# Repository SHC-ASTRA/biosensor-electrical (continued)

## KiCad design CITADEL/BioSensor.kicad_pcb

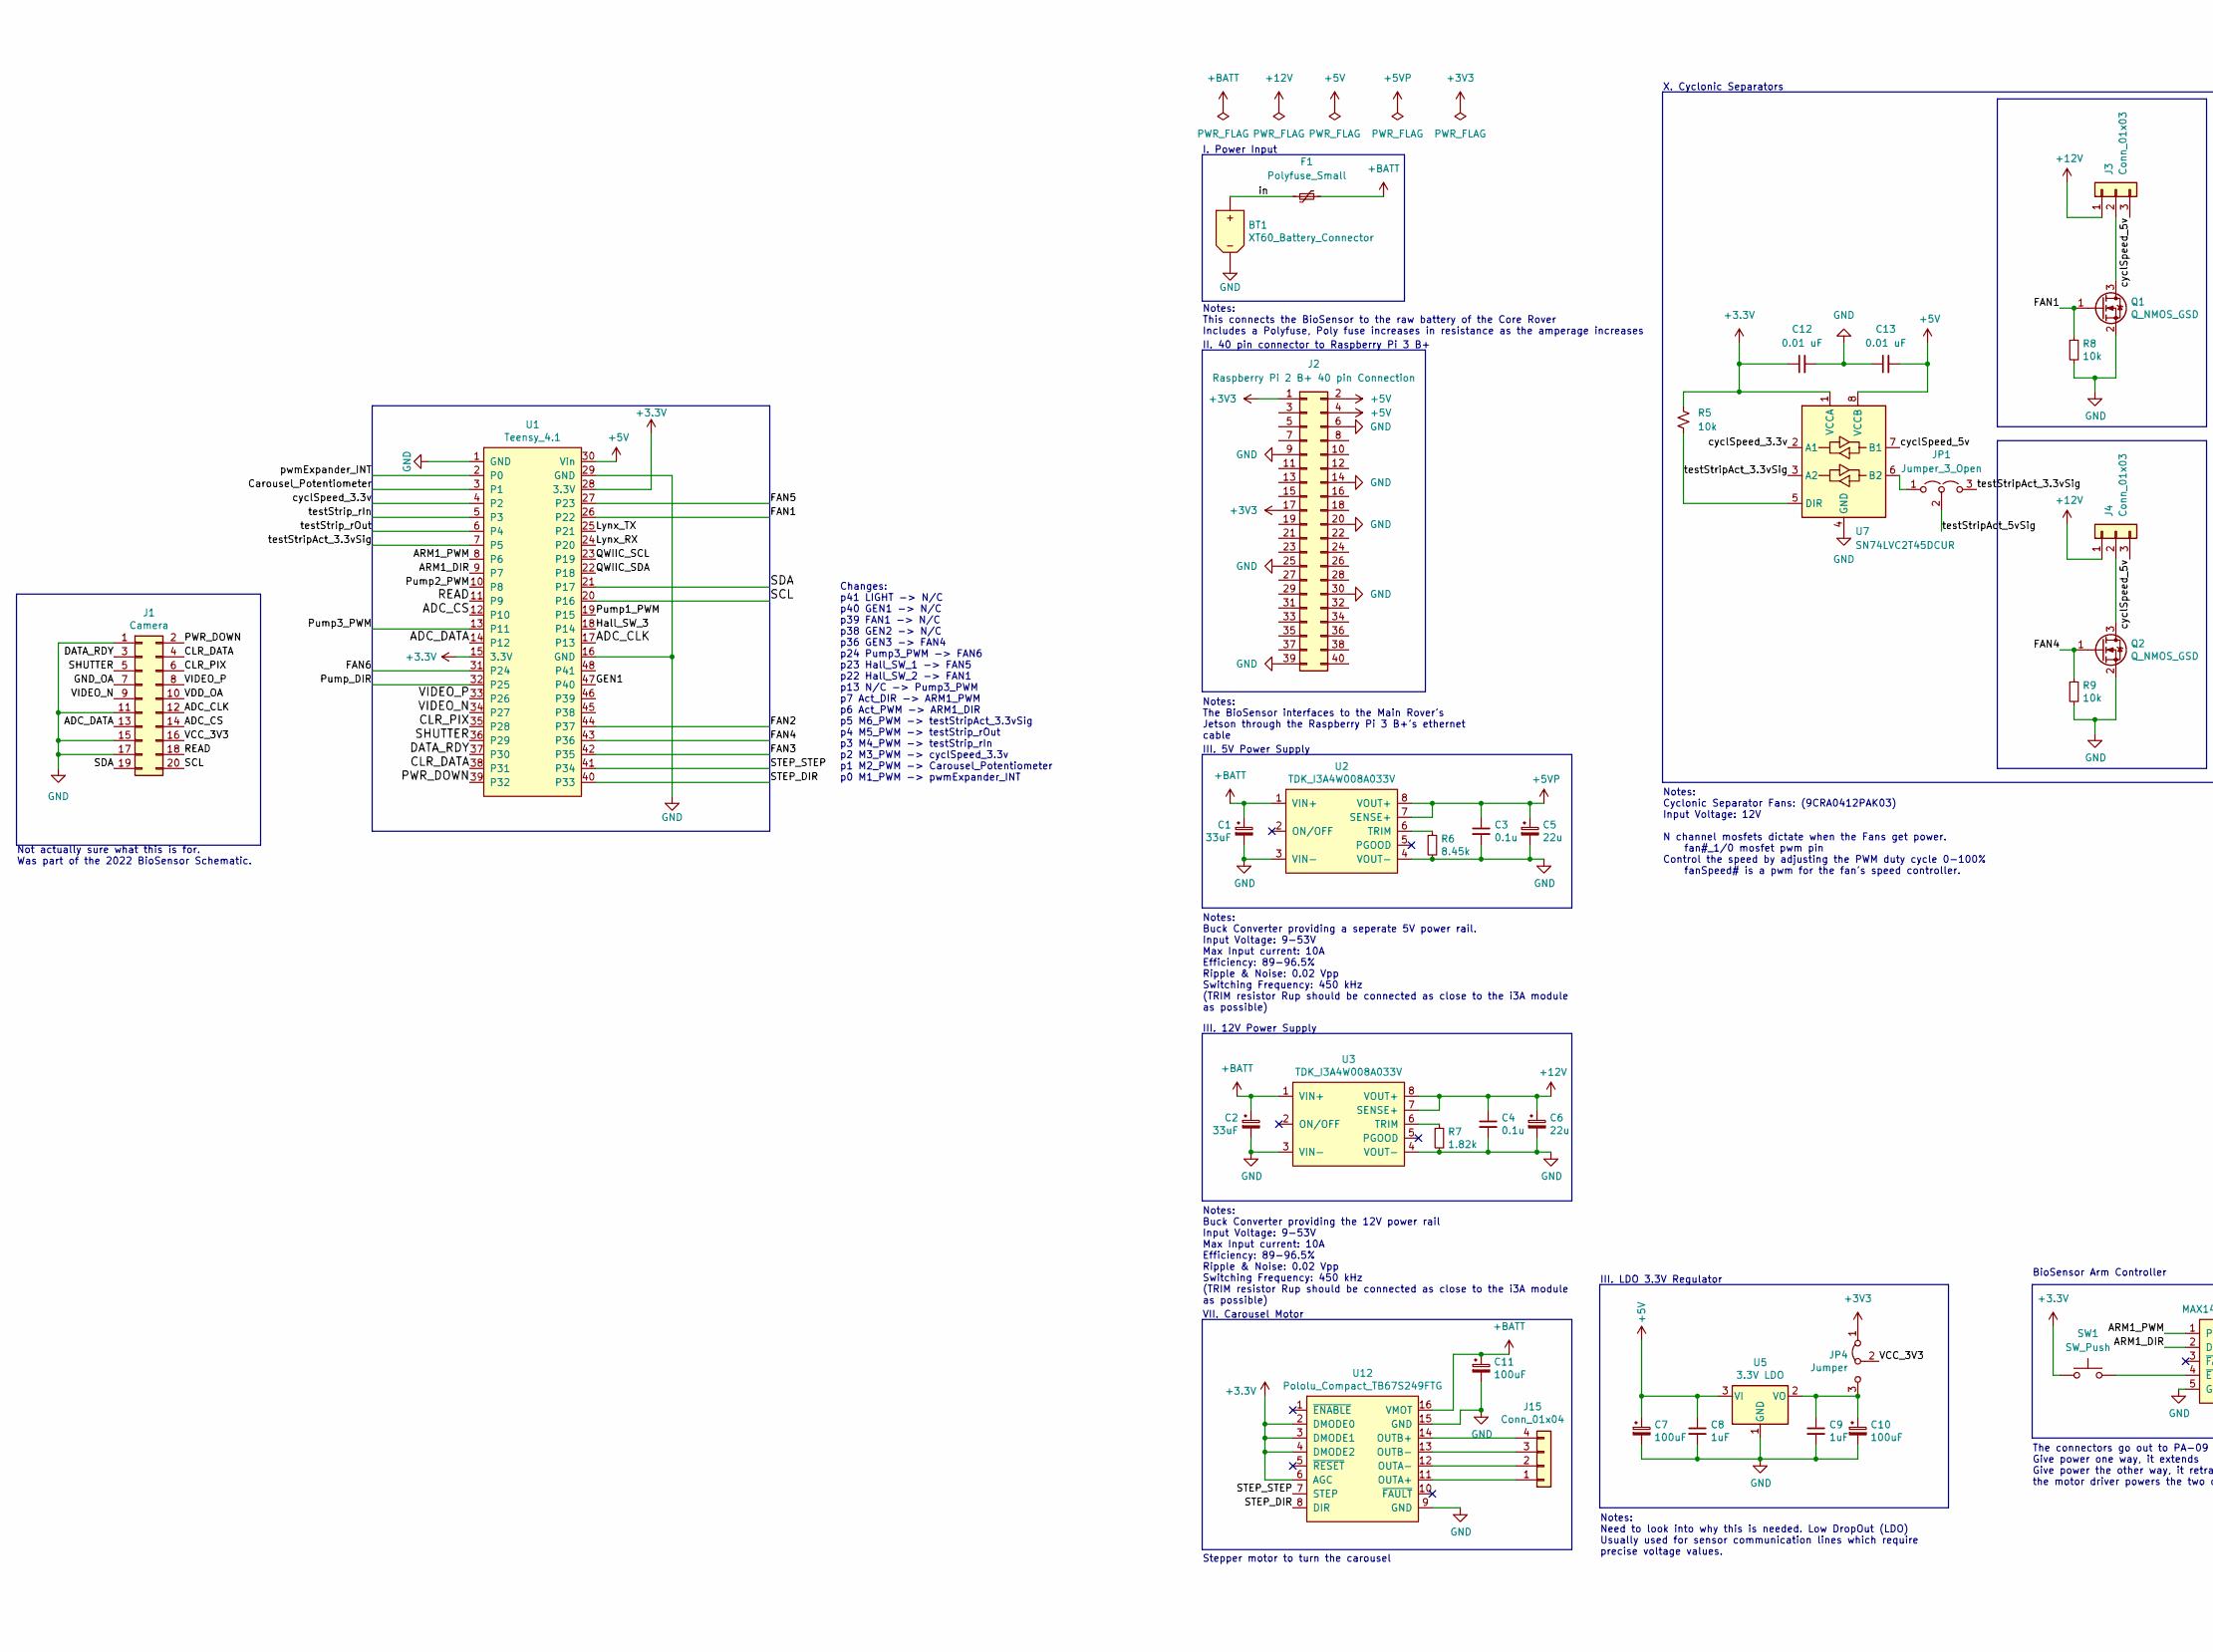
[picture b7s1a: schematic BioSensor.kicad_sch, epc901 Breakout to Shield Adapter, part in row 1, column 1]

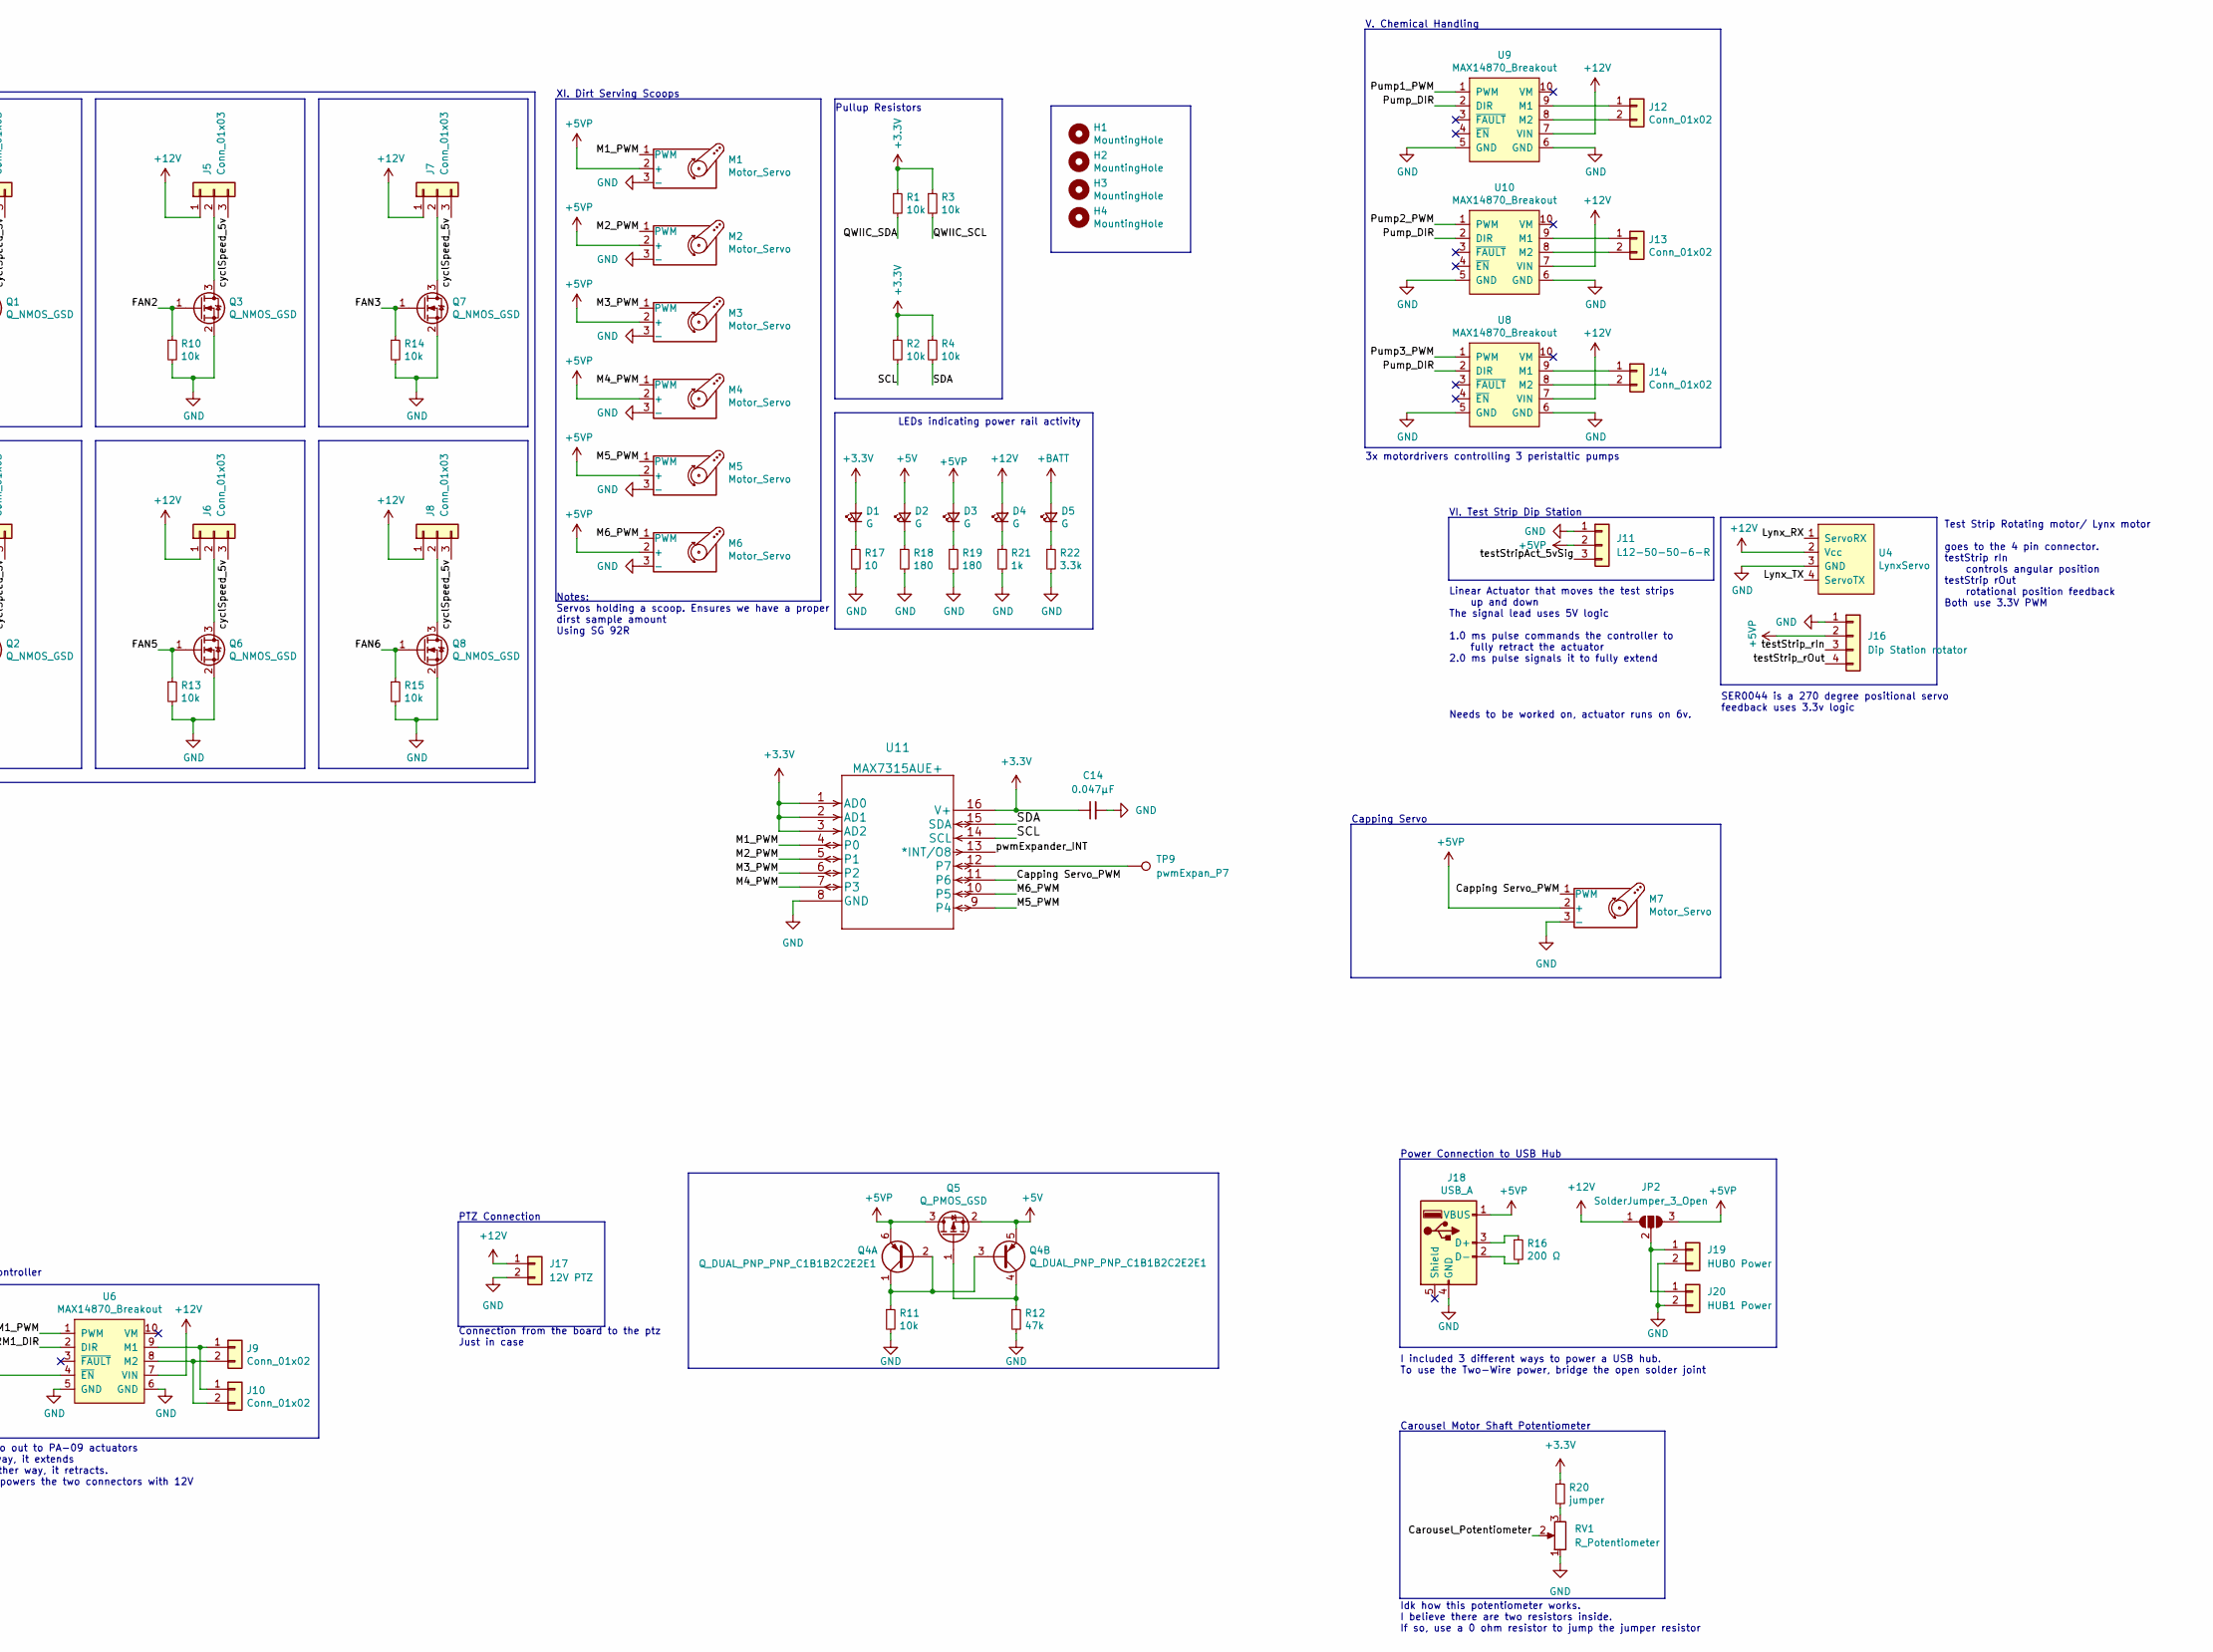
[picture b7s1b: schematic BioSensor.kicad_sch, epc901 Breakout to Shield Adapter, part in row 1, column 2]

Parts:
BT1: XT60_Battery_Connector; AMASS_XT60-M_1x02_P7.20mm_Vertical
C1, C2: 33uF; CP_Elec_10x10; Digikey Part Num 493-4402-1-ND
C3, C4: 0.1u; C_0603_1608Metric
C5, C6: 22u; CP_Elec_6.3x5.9; Digikey Part Num 493-4545-1-ND
C7, C10, C11: 100uF; C_Radial_D6.3mm_H7.0mm_P2.50mm; Digikey Part Num 1189-2182-ND
C8, C9: 1uF; C_0805_2012Metric; Digikey Part Num 1276-2928-1-ND
C12, C13: 0.01 uF; C_0603_1608Metric
C14: 0.047µF; C_0603_1608Metric_Pad1.08x0.95mm_HandSolder
D1, D2, D3, D4, D5: G; LED_0603_1608Metric_Pad1.05x0.95mm_HandSolder; Digikey Part Num 732-4971-1-ND
F1: Polyfuse_Small; Fuse_Littelfuse-LVR100
H1, H2, H3, H4: MountingHole; MountingHole_3.2mm_M3
J1: Camera; IDC-Header_2x10_P2.54mm_Vertical; Digikey Part Num S9172-ND
J2: Raspberry Pi 2 B+ 40 pin Connection; PinHeader_2x20_P2.54mm_Vertical
J3, J4, J5, J6, J7, J8: Conn_01x03; PinHeader_1x03_P2.54mm_Vertical
J9, J10, J12, J13, J14: Conn_01x02; JST_XH_B2B-XH-A_1x02_P2.50mm_Vertical
J11: L12-50-50-6-R; PinSocket_1x03_P2.54mm_Vertical
J15: Conn_01x04; JST_XH_B4B-XH-A_1x04_P2.50mm_Vertical
J16: Dip Station rotator; PinSocket_1x04_P2.54mm_Vertical
J17: 12V PTZ; JST_XH_B2B-XH-A_1x02_P2.50mm_Vertical
J18: USB_A; USB_A_Molex_67643_Horizontal; Digikey Part Num WM14667-ND
J19: HUB0 Power; JST_XH_B2B-XH-A_1x02_P2.50mm_Vertical
J20: HUB1 Power; JST_XH_B2B-XH-A_1x02_P2.50mm_Vertical
JP1: Jumper_3_Open; SolderJumper-3_P1.3mm_Open_RoundedPad1.0x1.5mm_NumberLabels
JP2: SolderJumper_3_Open; SolderJumper-3_P2.0mm_Open_TrianglePad1.0x1.5mm_NumberLabels
JP4: Jumper; PinHeader_1x03_P2.54mm_Vertical
M1, M2, M3, M4, M5, M6, M7: Motor_Servo; PinHeader_1x03_P2.54mm_Vertical
Q1, Q2, Q3, Q6, Q7, Q8: Q_NMOS_GSD; SOT-23; Digikey Part Num TSM210N02CXRFGCT-ND
Q4: Q_DUAL_PNP_PNP_C1B1B2C2E2E1; SOT-23-6; Digikey Part Num DMMT5401-FDICT-ND
Q5: Q_PMOS_GSD; SOT-23; Digikey Part Num SSM3J328RLFCT-ND
R1, R2, R3, R4, R5, R8, R9, R10, R11, R13, R14, R15: 10k; R_0603_1608Metric
R6: 8.45k; R_0603_1608Metric; Digikey Part Num 311-8.45KHRCT-ND
R7: 1.82k; R_0603_1608Metric; Digikey Part Num RMCF0603FT1K82CT-ND
R12: 47k; R_0603_1608Metric; Digikey Part Num 311-47.0KHRCT-ND
R16: 200 Ω; R_0603_1608Metric; Digikey Part Num RMCF0603FT200RCT-ND
R17: 10; R_0603_1608Metric; Digikey Part Num 311-10.0HRCT-ND
R18, R19: 180; R_0603_1608Metric; Digikey Part Num 311-180HRCT-ND
R20: jumper; R_0603_1608Metric
R21: 1k; R_0603_1608Metric; Digikey Part Num 311-1.00KHRCT-ND
R22: 3.3k; R_0603_1608Metric; Digikey Part Num 311-3.30KHRCT-ND
RV1: R_Potentiometer; JST_XH_B3B-XH-AM_1x03_P2.50mm_Vertical
SW1: SW_Push; JST_PH_B2B-PH-K_1x02_P2.00mm_Vertical
TP9: pwmExpan_P7; TestPoint_THTPad_2.0x2.0mm_Drill1.0mm
U1: Teensy_4.1; Teensy4.1; Digikey Part Num 1568-DEV-16771-ND
U2, U3: TDK_I3A4W008A033V; Power_Supply_32nd_Brick; Digikey Part Num 285-2720-ND
U4: LynxServo; Molex_SPOX_5268-04A_1x04_P2.50mm_Horizontal; Digikey Part Num 23-0022057045-ND
U5: 3.3V LDO; SOT-223-3_TabPin2; Digikey Part Num ZLDO1117G33DICT-ND
U6, U8, U9, U10: MAX14870_Breakout; Pololu_2961; Digikey Part Num 2183-2961-ND
U7: SN74LVC2T45DCUR; VSSOP-8_2.4x2.1mm_P0.5mm
U11: MAX7315AUE+; MAX7315AUE&plus_
U12: Pololu_Compact_TB67S249FTG; DIP-16_500; Digikey Part Num 2183-3096-ND

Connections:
+5V: C7.1, C8.1, C13.2, D2.2 (A), J2.2, J2.4, Q4.5 (E2), Q5.2 (S), U1.30 (Vin), U5.3 (VI), U7.8 (VCCB)
+5VP: C3.1, C5.1, D3.2 (A), J11.2, J16.2, J18.1 (VBUS), JP2.3 (B), M1.2 (+), M2.2 (+), M3.2 (+), M4.2 (+), M5.2 (+), M6.2 (+), M7.2 (+), Q4.6 (E1), Q5.3 (D), U2.7 (SENSE+), U2.8 (VOUT+)
+12V: C4.1, C6.1, D4.2 (A), J3.1, J4.1, J5.1, J6.1, J7.1, J8.1, J17.1, JP2.1 (A), U3.7 (SENSE+), U3.8 (VOUT+), U4.2 (Vcc), U6.7 (VIN), U8.7 (VIN), U9.7 (VIN), U10.7 (VIN)
+BATT: C1.1, C2.1, C11.1, D5.2 (A), F1.1, U2.1 (VIN+), U3.1 (VIN+), U12.16 (VMOT)
/ADC_CLK: J1.12, U1.17 (P13)
/ADC_CS: J1.14, U1.12 (P10)
/ADC_DATA: J1.13, U1.14 (P12)
/ARM1_DIR: U1.9 (P7), U6.2 (DIR)
/ARM1_PWM: U1.8 (P6), U6.1 (PWM)
/CLR_DATA: J1.4, U1.38 (P31)
/CLR_PIX: J1.6, U1.35 (P28)
/Capping Servo_PWM: M7.1 (PWM), U11.11 (P6)
/Carousel_Potentiometer: RV1.2, U1.3 (P1)
/DATA_RDY: J1.3, U1.37 (P30)
/FAN1: Q1.1 (G), R8.1, U1.26 (P22)
/FAN2: Q3.1 (G), R10.1, U1.44 (P37)
/FAN3: Q7.1 (G), R14.1, U1.42 (P35)
/FAN4: Q2.1 (G), R9.1, U1.43 (P36)
/FAN5: Q6.1 (G), R13.1, U1.27 (P23)
/FAN6: Q8.1 (G), R15.1, U1.31 (P24)
/GEN1: U1.47 (P40)
/GND_OA: J1.7
/Hall_SW_3: U1.18 (P14)
/Lynx_RX: U1.24 (P20), U4.1 (ServoRX)
/Lynx_TX: U1.25 (P21), U4.4 (ServoTX)
/M1_PWM: M1.1 (PWM), U11.4 (P0)
/M2_PWM: M2.1 (PWM), U11.5 (P1)
/M3_PWM: M3.1 (PWM), U11.6 (P2)
/M4_PWM: M4.1 (PWM), U11.7 (P3)
/M5_PWM: M5.1 (PWM), U11.9 (P4)
/M6_PWM: M6.1 (PWM), U11.10 (P5)
/PWR_DOWN: J1.2, U1.39 (P32)
/Pump1_PWM: U1.19 (P15), U9.1 (PWM)
/Pump2_PWM: U1.10 (P8), U10.1 (PWM)
/Pump3_PWM: U1.13 (P11), U8.1 (PWM)
/Pump_DIR: U1.32 (P25), U8.2 (DIR), U9.2 (DIR), U10.2 (DIR)
/QWIIC_SCL: R3.2, U1.23 (P19)
/QWIIC_SDA: R1.2, U1.22 (P18)
/READ: J1.18, U1.11 (P9)
/SCL: J1.20, R2.2, U1.20 (P16), U11.14 (SCL)
/SDA: J1.19, R4.2, U1.21 (P17), U11.15 (SDA)
/SHUTTER: J1.5, U1.36 (P29)
/STEP_DIR: U1.40 (P33), U12.8 (DIR)
/STEP_STEP: U1.41 (P34), U12.7 (STEP)
/VCC_3V3: J1.16, JP4.2 (C)
/VDD_OA: J1.10
/VIDEO_N: J1.9, U1.34 (P27)
/VIDEO_P: J1.8, U1.33 (P26)
/cyclSpeed_3.3v: U1.4 (P2), U7.2 (A1)
/cyclSpeed_5v: J3.3, J4.3, J5.3, J6.3, J7.3, J8.3, U7.7 (B1)
/in: BT1.2 (Pos), F1.2
/pwmExpander_INT: U1.2 (P0), U11.13 (*INT/O8)
/testStripAct_3.3vSig: JP1.3 (B), U1.7 (P5), U7.3 (A2)
/testStripAct_5vSig: J11.3, JP1.2 (C)
/testStrip_rIn: J16.3, U1.5 (P3)
/testStrip_rOut: J16.4, U1.6 (P4)
GND: BT1.1 (Neg), C1.2, C2.2, C3.2, C4.2, C5.2, C6.2, C7.2, C8.2, C9.2, C10.2, C11.2, C12.2, C13.1, C14.2, J1.1, J1.11, J1.15, J1.17, J2.6, J2.9, J2.14, J2.20, J2.25, J2.30, J2.39, J11.1, J16.1, J17.2, J18.4 (GND), J19.2, J20.2, M1.3 (-), M2.3 (-), M3.3 (-), M4.3 (-), M5.3 (-), M6.3 (-), M7.3 (-), Q1.2 (S), Q2.2 (S), Q3.2 (S), Q6.2 (S), Q7.2 (S), Q8.2 (S), R6.2, R7.2, R8.2, R9.2, R10.2, R11.2, R12.2, R13.2, R14.2, R15.2, R17.2, R18.2, R19.2, R21.2, R22.2, RV1.1, U1.1 (GND), U1.16 (GND), U1.29 (GND), U2.3 (VIN-), U2.4 (VOUT-), U3.3 (VIN-), U3.4 (VOUT-), U4.3 (GND), U5.1 (GND), U6.5 (GND), U6.6 (GND), U7.4 (GND), U8.5 (GND), U8.6 (GND), U9.5 (GND), U9.6 (GND), U10.5 (GND), U10.6 (GND), U11.8 (GND), U12.9 (GND), U12.15 (GND)
unnamed: C9.1, C10.1, JP4.3 (B), U5.2 (VO)
unnamed: D1.1 (K), R17.1
unnamed: D2.1 (K), R18.1
unnamed: D3.1 (K), R19.1
unnamed: D4.1 (K), R21.1
unnamed: D5.1 (K), R22.1
unnamed: J3.2, Q1.3 (D)
unnamed: J4.2, Q2.3 (D)
unnamed: J5.2, Q3.3 (D)
unnamed: J6.2, Q6.3 (D)
unnamed: J7.2, Q7.3 (D)
unnamed: J8.2, Q8.3 (D)
unnamed: J9.1, J10.1, U6.9 (M1)
unnamed: J9.2, J10.2, U6.8 (M2)
unnamed: J12.1, U9.9 (M1)
unnamed: J12.2, U9.8 (M2)
unnamed: J13.1, U10.9 (M1)
unnamed: J13.2, U10.8 (M2)
unnamed: J14.1, U8.9 (M1)
unnamed: J14.2, U8.8 (M2)
unnamed: J15.1, U12.11 (OUTA+)
unnamed: J15.2, U12.12 (OUTA-)
unnamed: J15.3, U12.13 (OUTB-)
unnamed: J15.4, U12.14 (OUTB+)
unnamed: J18.2 (D-), R16.2
unnamed: J18.3 (D+), R16.1
unnamed: J19.1, J20.1, JP2.2 (C)
unnamed: JP1.1 (A), U7.6 (B2)
unnamed: Q4.1 (C1), Q4.2 (B1), Q4.3 (B2), R11.1
unnamed: Q4.4 (C2), Q5.1 (G), R12.1
unnamed: R5.2, U7.5 (DIR)
unnamed: R6.1, U2.6 (TRIM)
unnamed: R7.1, U3.6 (TRIM)
unnamed: R20.2, RV1.3
unnamed: SW1.2, U6.4 (~EN)
unnamed: TP9.1, U11.12 (P7)

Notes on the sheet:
V. Chemical Handling
III. 5V Power Supply
III. 12V Power Supply
SER0044 is a 270 degree positional servo feedback uses 3.3v logic
BioSensor Arm Controller
Notes: This connects the BioSensor to the raw battery of the Core Rover Includes a Polyfuse, Poly fuse increases in resistance as the amperage increases
III. LDO 3.3V Regulator
II. 40 pin connector to Raspberry Pi 3 B+
Notes: Buck Converter providing the 12V power rail Input Voltage: 9-53V Max Input current: 10A Efficiency: 89-96.5% Ripple & Noise: 0.02 Vpp Switching Frequency: 450 kHz (TRIM resistor Rup should be connected as close to the i3A module as possible)
Stepper motor to turn the carousel
Notes: The BioSensor interfaces to the Main Rover's Jetson through the Raspberry Pi 3 B+'s ethernet cable
Connection from the board to the ptz Just in case
Carousel Motor Shaft Potentiometer
Test Strip Rotating motor/ Lynx motor goes to the 4 pin connector. testStrip rIn controls angular position testStrip rOut rotational position feedback Both use 3.3V PWM
I. Power Input
Notes: Need to look into why this is needed. Low DropOut (LDO) Usually used for sensor communication lines which require precise voltage values.
VII. Carousel Motor
Not actually sure what this is for. Was part of the 2022 BioSensor Schematic.
Changes: p41 LIGHT -> N/C p40 GEN1 -> N/C p39 FAN1 -> N/C p38 GEN2 -> N/C p36 GEN3 -> FAN4 p24 Pump3_PWM -> FAN6 p23 Hall_SW_1 -> FAN5 p22 Hall_SW_2 -> FAN1 p13 N/C -> Pump3_PWM p7 Act_DIR -> ARM1_PWM p6 Act_PWM -> ARM1_DIR p5 M6_PWM -> testStripAct_3.3vSig p4 M5_PWM -> testStrip_rOut p3 M4_PWM -> 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
The connectors go out to PA-09 actuators Give power one way, it extends Give power the other way, it retracts. the motor driver powers the two connectors with 12V
Linear Actuator that moves the test strips up and down The signal lead uses 5V logic 1.0 ms pulse commands the controller to fully retract the actuator 2.0 ms pulse signals it to fully extend Needs to be worked on, actuator runs on 6v.
PTZ Connection
Notes: Cyclonic Separator Fans: (9CRA0412PAK03) Input Voltage: 12V N channel mosfets dictate when the Fans get power. fan#_1/0 mosfet pwm pin Control the speed by adjusting the PWM duty cycle 0-100% fanSpeed# is a pwm for the fan's speed controller.
Pullup Resistors
Notes: Buck Converter providing a seperate 5V power rail. Input Voltage: 9-53V Max Input current: 10A Efficiency: 89-96.5% Ripple & Noise: 0.02 Vpp Switching Frequency: 450 kHz (TRIM resistor Rup should be connected as close to the i3A module as possible)
XI. Dirt Serving Scoops
3x motordrivers controlling 3 peristaltic pumps
Capping Servo
Power Connection to USB Hub
Idk how this potentiometer works. I believe there are two resistors inside. If so, use a 0 ohm resistor to jump the jumper resistor
LEDs indicating power rail activity
X. Cyclonic Separators
Notes: Servos holding a scoop. Ensures we have a proper dirst sample amount Using SG 92R
I included 3 different ways to power a USB hub. To use the Two-Wire power, bridge the open solder joint
VI. Test Strip Dip Station

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
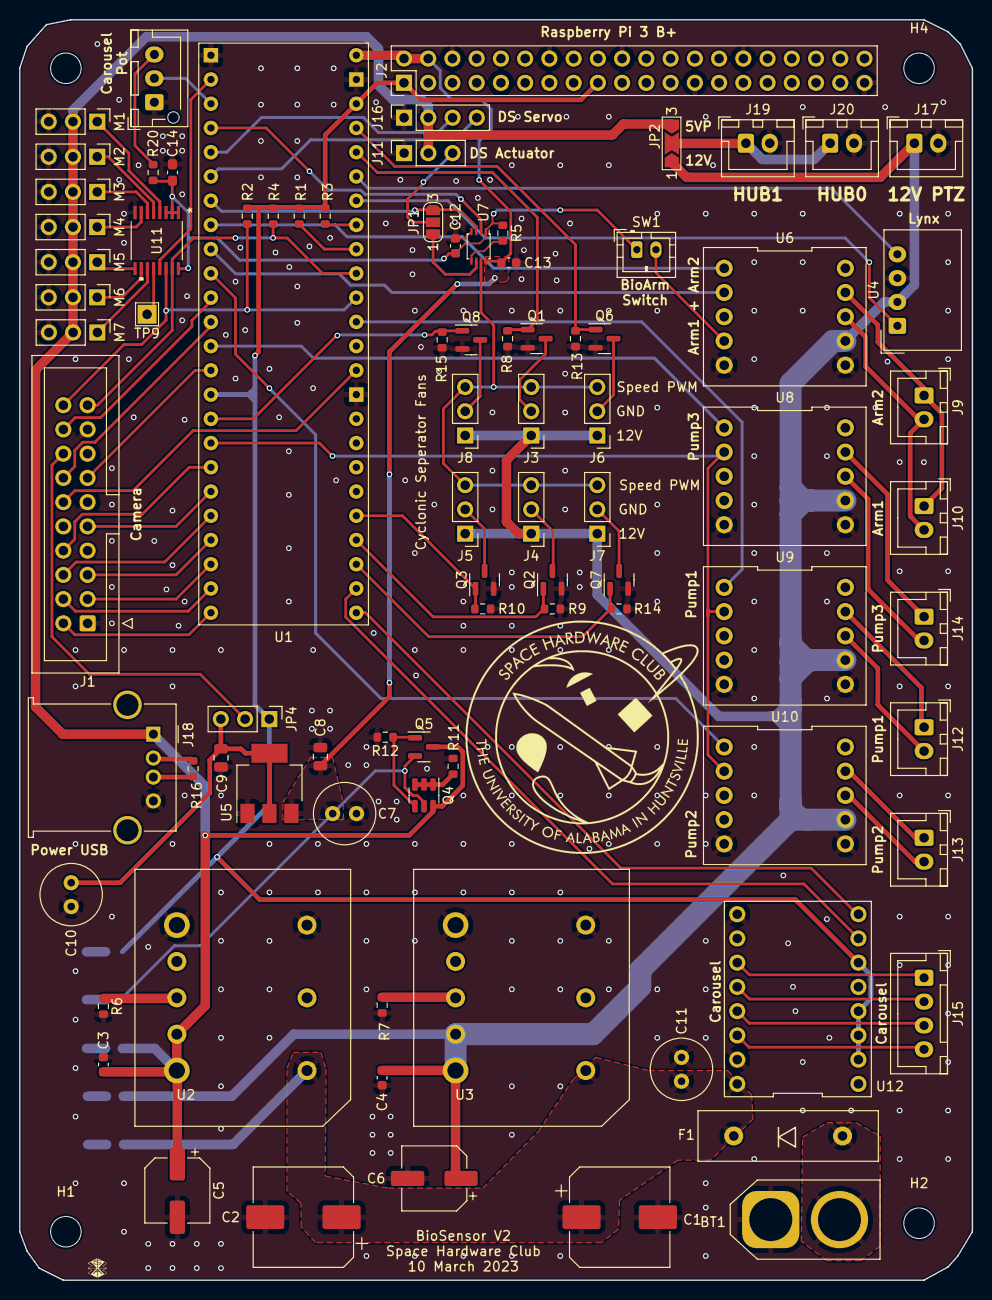
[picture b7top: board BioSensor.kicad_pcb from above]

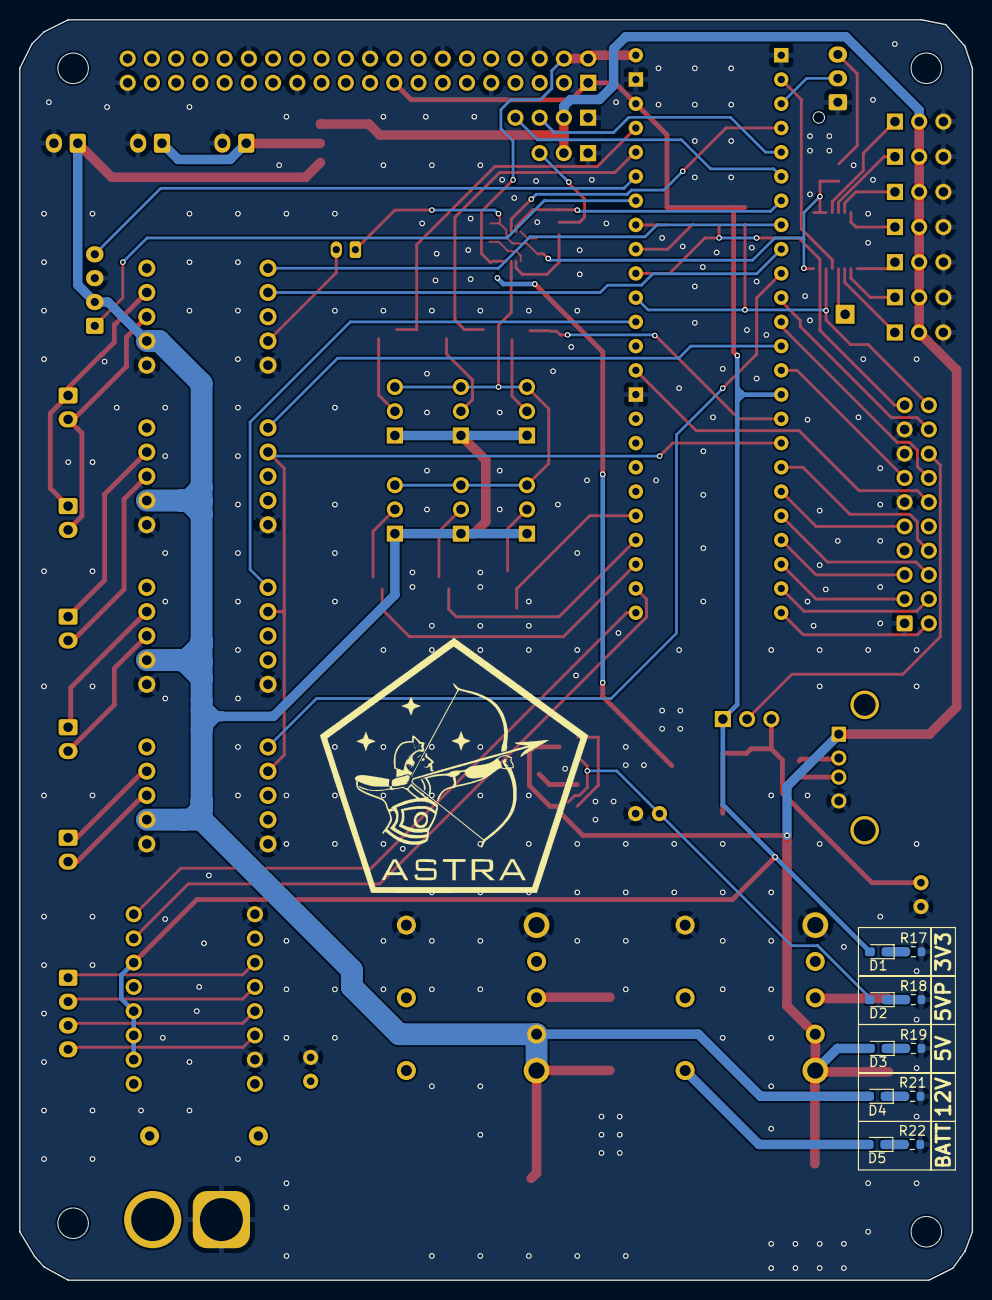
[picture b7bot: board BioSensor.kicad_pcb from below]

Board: 2 copper layers, 99.8 x 132.1 mm, 100 parts (10 on the bottom side), 91 nets.

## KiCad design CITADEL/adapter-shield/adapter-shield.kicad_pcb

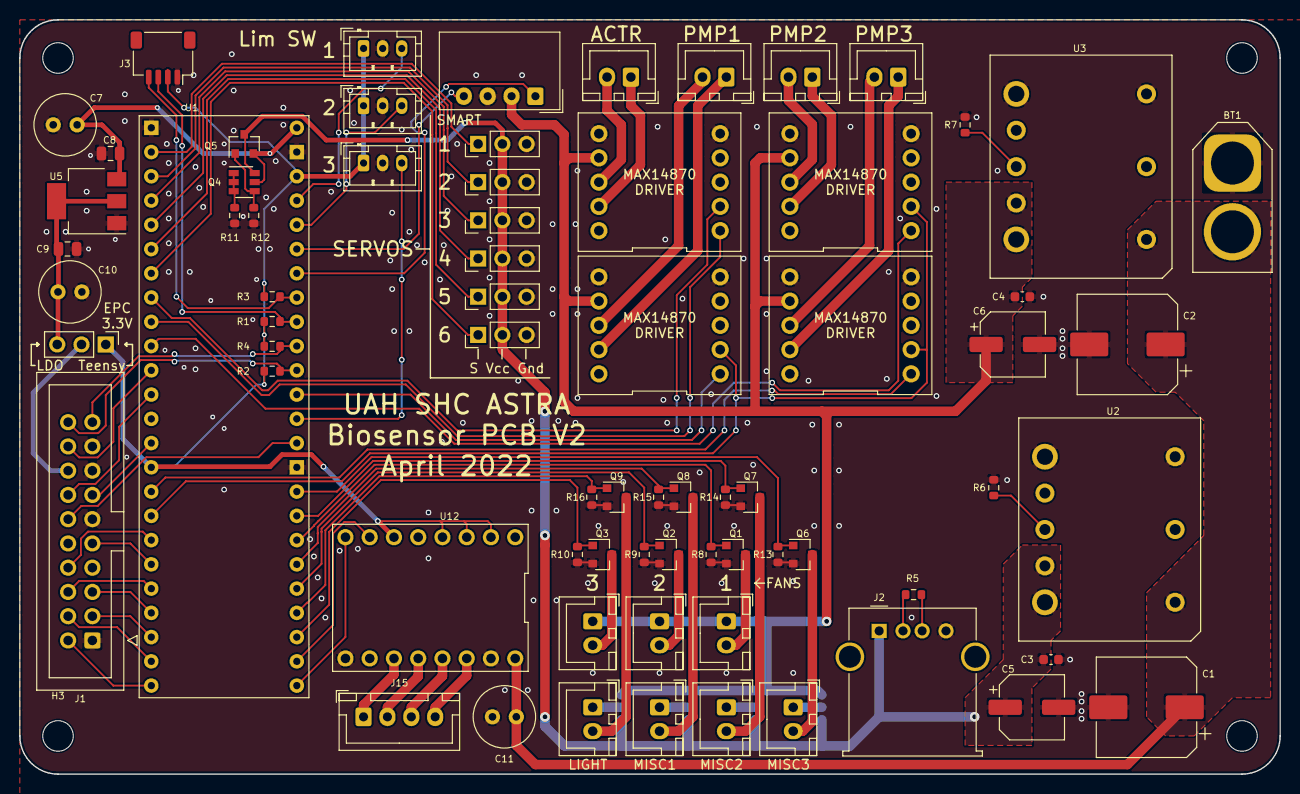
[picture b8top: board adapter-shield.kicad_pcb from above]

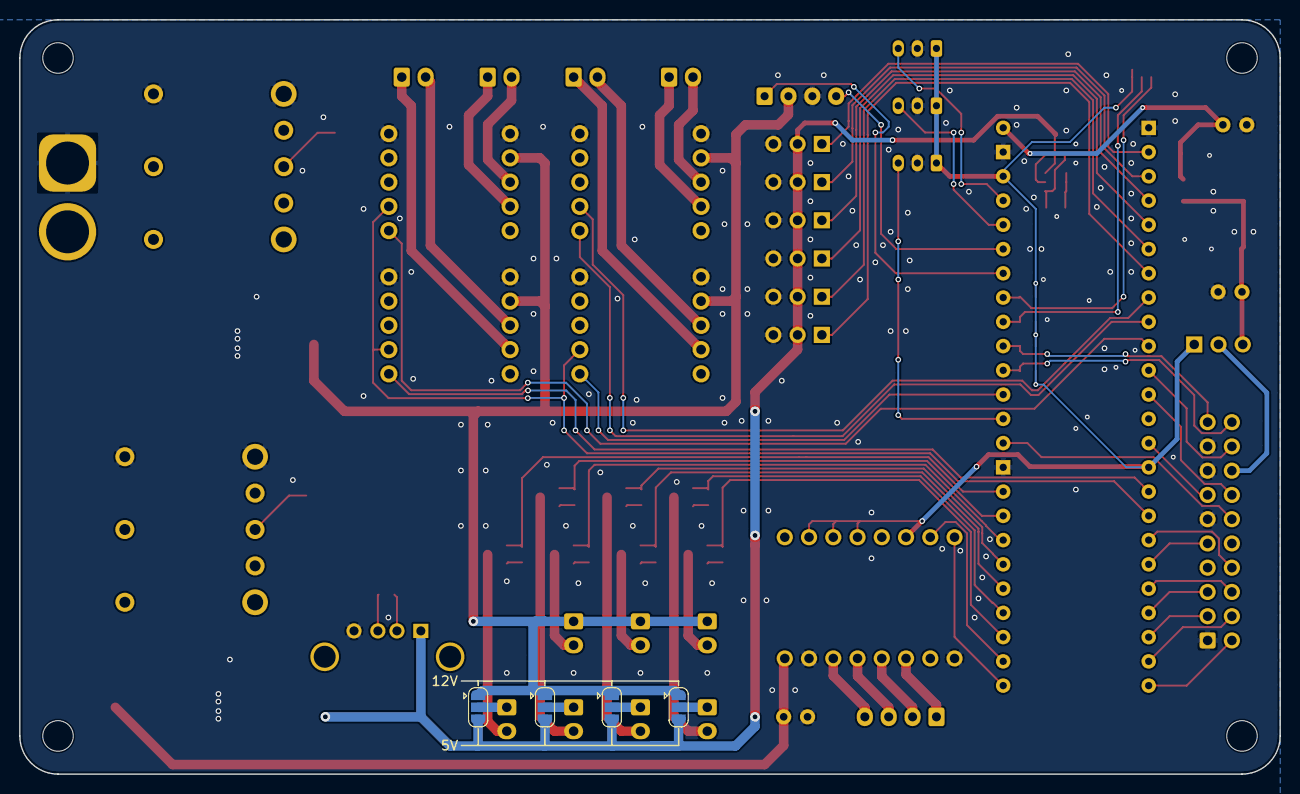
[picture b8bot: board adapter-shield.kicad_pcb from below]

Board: 2 copper layers, 132.0 x 79.0 mm, 80 parts (4 on the bottom side), 78 nets.

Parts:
BT1: XT60_Battery_Connector; AMASS_XT60-M_1x02_P7.20mm_Vertical
C1, C2: 33u; CP_Elec_10x10
C3, C4: 0.1u; C_0603_1608Metric
C5, C6: 22u; CP_Elec_6.3x5.9
C7, C10, C11: 100uF; C_Radial_D6.3mm_H7.0mm_P2.50mm
C8, C9: 1uF; C_0805_2012Metric
H1, H2, H3, H4: MountingHole; MountingHole_3.2mm_M3
J1: Camera; IDC-Header_2x10_P2.54mm_Vertical
J2: USB_A; USB_A_Molex_67643_Horizontal
J3: QWIIC_Generic_Conn; JST_SH_SM04B-SRSS-TB_1x04-1MP_P1.00mm_Horizontal
J4, J5, J6, J7, J8, J9, J10, J11, J12, J13, J14: Conn_01x02; JST_XH_B2B-XH-A_1x02_P2.50mm_Vertical
J15: Conn_01x04; JST_XH_B4B-XH-A_1x04_P2.50mm_Vertical
JP1, JP2, JP3, JP5: SolderJumper_3_Open; SolderJumper-3_P1.3mm_Open_RoundedPad1.0x1.5mm
JP4: Jumper; PinHeader_1x03_P2.54mm_Vertical
M1, M2, M3, M4, M5, M6: Motor_Servo; PinHeader_1x03_P2.54mm_Vertical
Q1, Q2, Q3, Q6, Q7, Q8, Q9: Q_NMOS_GSD; SOT-23
Q4: Q_DUAL_PNP_PNP_C1B1B2C2E2E1; SOT-23-6
Q5: Q_PMOS_GSD; SOT-23
R1, R2, R3, R4, R8, R9, R10, R11, R13, R14, R15, R16: 10k; R_0603_1608Metric
R5: 200; R_0603_1608Metric
R6: 8.45k; R_0603_1608Metric
R7: 1.82k; R_0603_1608Metric
R12: 47k; R_0603_1608Metric
U1: Teensy_4.1; Teensy4.1
U2, U3: TDK_I3A4W008A033V; Power_Supply_32nd_Brick
U4: LynxServo; Molex_SPOX_5268-04A_1x04_P2.50mm_Horizontal
U5: 3.3V LDO; SOT-223-3_TabPin2
U6, U7, U13: AH1815-P-B; JST_PH_B3B-PH-K_1x03_P2.00mm_Vertical
U8, U9, U10, U11: MAX14870_Breakout; Pololu_2961
U12: Pololu_Compact_TB67S249FTG; DIP-16_500

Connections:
+3V3: J3.2, JP4.1, R1.1, R2.1, R3.1, R4.1, U1.15, U1.28, U6.1, U7.1, U12.2, U12.3, U12.4, U12.6, U13.1
+5V: C7.1, C8.1, Q4.5, Q5.2, U1.30, U5.3
+5VP: C3.1, C5.1, J2.1, JP1.3, JP2.3, JP3.3, JP5.3, M1.2, M2.2, M3.2, M4.2, M5.2, M6.2, Q4.6, Q5.3, U2.7, U2.8
+12V: C4.1, C6.1, J4.1, J5.1, J6.1, JP1.1, JP2.1, JP3.1, JP5.1, U3.7, U3.8, U4.2, U8.7, U9.7, U10.7, U11.7
/ADC_CLK: J1.12, U1.17
/ADC_CS: J1.14, U1.12
/ADC_DATA: J1.13, U1.14
/Act_DIR: U1.8, U8.2
/Act_PWM: U1.9, U8.1
/CLR_DATA: J1.4, U1.38
/CLR_PIX: J1.6, U1.35
/DATA_RDY: J1.3, U1.37
/FAN1: Q1.1, R8.1, U1.46
/FAN2: Q2.1, R9.1, U1.44
/FAN3: Q3.1, R10.1, U1.42
/GEN1: Q7.1, R14.1, U1.47
/GEN2: Q8.1, R15.1, U1.45
/GEN3: Q9.1, R16.1, U1.43
/Hall_SW_1: U1.27, U6.3
/Hall_SW_2: U1.26, U7.3
/Hall_SW_3: U1.18, U13.3
/LIGHT: Q6.1, R13.1, U1.48
/Lynx_RX: U1.24, U4.1
/Lynx_TX: U1.25, U4.4
/M1_PWM: M1.1, U1.2
/M2_PWM: M2.1, U1.3
/M3_PWM: M3.1, U1.4
/M4_PWM: M4.1, U1.5
/M5_PWM: M5.1, U1.6
/M6_PWM: M6.1, U1.7
/PWR_DOWN: J1.2, U1.39
/Pump1_PWM: U1.19, U9.1
/Pump2_PWM: U1.10, U10.1
/Pump3_PWM: U1.31, U11.1
/Pump_DIR: U1.32, U9.2, U10.2, U11.2
/QWIIC_SCL: J3.4, R3.2, U1.23
/QWIIC_SDA: J3.3, R1.2, U1.22
/READ: J1.18, U1.11
/SCL: J1.20, R2.2, U1.20
/SDA: J1.19, R4.2, U1.21
/SHUTTER: J1.5, U1.36
/STEP_DIR: U1.40, U12.8
/STEP_STEP: U1.41, U12.7
/VCC_3V3: J1.16, JP4.2
/VIDEO_N: J1.9, U1.34
/VIDEO_P: J1.8, U1.33
/V_BAT: BT1.2, C1.1, C2.1, C11.1, U2.1, U3.1, U12.16
GND: BT1.1, C1.2, C2.2, C3.2, C4.2, C5.2, C6.2, C7.2, C8.2, C9.2, C10.2, C11.2, J1.1, J1.11, J1.15, J1.17, J2.4, J3.1, M1.3, M2.3, M3.3, M4.3, M5.3, M6.3, Q1.2, Q2.2, Q3.2, Q6.2, Q7.2, Q8.2, Q9.2, R6.2, R7.2, R8.2, R9.2, R10.2, R11.2, R12.2, R13.2, R14.2, R15.2, R16.2, U1.1, U1.16, U1.29, U2.3, U2.4, U3.3, U3.4, U4.3, U5.1, U6.2, U7.2, U8.5, U8.6, U9.5, U9.6, U10.5, U10.6, U11.5, U11.6, U12.9, U12.15, U13.2
unnamed: C9.1, C10.1, JP4.3, U5.2
unnamed: J2.2, R5.2
unnamed: J2.3, R5.1
unnamed: J4.2, Q1.3
unnamed: J5.2, Q2.3
unnamed: J6.2, Q3.3
unnamed: J7.1, JP1.2
unnamed: J7.2, Q6.3
unnamed: J8.1, JP2.2
unnamed: J8.2, Q7.3
unnamed: J9.1, JP3.2
unnamed: J9.2, Q8.3
unnamed: J10.1, JP5.2
unnamed: J10.2, Q9.3
unnamed: J11.1, U8.9
unnamed: J11.2, U8.8
unnamed: J12.1, U9.9
unnamed: J12.2, U9.8
unnamed: J13.1, U10.9
unnamed: J13.2, U10.8
unnamed: J14.1, U11.9
unnamed: J14.2, U11.8
unnamed: J15.1, U12.11
unnamed: J15.2, U12.12
unnamed: J15.3, U12.13
unnamed: J15.4, U12.14
unnamed: Q4.1, Q4.2, Q4.3, R11.1
unnamed: Q4.4, Q5.1, R12.1
unnamed: R6.1, U2.6
unnamed: R7.1, U3.6

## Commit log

2025-12-13 CITADEL V1
    Sep 21, 2021; Thomas Bennett
2025-12-13 CITADEL V2
    April 14, 2022; Thomas Bennett
2025-12-13 CITADEL 2023 V2
    March 10, 2023; it was still just called 'BioSensor' and they added a carousel system
2025-12-13 CITADEL 2024 V2, FAERIE 2024 V2
    CITADEL January 17, 2024; FAERIE March 30, 2024; CITADEL was redesigned to be much simpler, FAERIE was introduced and designed by yours truly
2025-12-13 CITADEL 2025 V1, FAERIE 2025 V1
    CITADEL January 27, 2025; FAERIE January 26, 2025; Katherine and Mason did CITADEL, Reymund did FAERIE
2025-12-13 CITADEL 2025 V2
    April 8, 2025; replaced the second MCU with a GPIO extender IC that didn't end up working
2025-12-13 CITADEL 2025 V3
    May 11, 2025; got rid of the GPIO extender
2025-12-18 Started new CITADEL PCB
2026-01-10 Updated Schematic
2026-01-14 Updated Schematic
    Changed MCU, added additional connectors
2026-01-14 Updated Schematic
    Changed motor drivers and connectors
2026-01-16 Changed 5V buck from 15A to 11A
2026-01-16 Added no connect flags
2026-01-18 Started PCB V1
2026-01-19 Updated PCB V1
2026-01-22 Added camera connectors
2026-01-23 Added camera connections
2026-01-24 Changed servo connectors, added connector for servo daughter board
2026-01-24 Created servo daughter board
2026-01-24 Changed board to be square
2026-01-25 Added ASTRA logo
2026-01-26 Fixed typo with stepper connectors
2026-01-30 Added PCA9685 servo controller
2026-01-30 Excluded unneeded error flags
2026-01-30 Fixed typo with stepper daughter connector
2026-01-31 Updated servo connectors and ESC comms
2026-01-31 Updated servo connectors
2026-01-31 Added I²C pullups
2026-01-31 Removed error for custom courtyard
2026-02-06 Changed back plane to GND and added 5V zone
2026-02-06 Updated PCB as per review feedback
    Changed routing of vibration motor trace and removed unused EPS32 pin
2026-02-06 Changed 5V trace for PCA9685
2026-02-07 Updated PCB as per feedback
2026-02-07 Aligned vias to grid
2026-02-07 Changed trace for vibration motor
2026-02-10 Updated ESP32 Footprint
2026-02-10 Updated Vias
2026-02-11 Moved vias away from trace
2026-03-19 Changed layout to support new linear actuators
2026-03-20 Updated reference names
2026-03-20 Created CITADEL V2
2026-03-20 Moved V1 files to dedicated folder
2026-03-21 Cleaned up a trace
2026-03-23 Removed stepper drivers
2026-03-23 Removed steppers and updated silkscreen names
2026-03-25 Removed daughter board
    Board was no longer needed, connections were moved to main CITADEL board
2026-03-25 Changed linear actuator connectors
    Removed the connector for the daughter board and moved the 1x2 molex connectors onto main board
2026-04-16 FAERIE 2026 V1
    FAERIE April 15, 2026
2026-04-16 Updated values for CAN resistors and caps
2026-04-21 FAERIE 2026 r1.01
    Changed Sparkmax PWM 1 and 2 from XT-30 connectors to Molex
2026-04-22 FAERIE 2026 r1.02
    Built ground plane for change to Sparkmax PWM Molex connectors
2026-04-22 LANCE 2026 r1
    Rename of FAERIE r1.02 to LANCE r1
2026-04-22 LANCE 2026 r1.01
    A1 Pin 8 pad connection changed to solid
2026-05-01 LANCE 2026 r1.02
    Changed nSLEEP on MP6603 (x2) and on MPQ6612A to 3.3V, moved CAN_TX to non-strapping pin 9 on ESP32, changed SHT30 connector to I2C connector convention used on Core and Antenna, moved SHT30 connecto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
2026-05-26 feat!: remove faerie
